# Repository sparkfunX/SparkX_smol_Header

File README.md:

# SparkX smôl Header

[*SparkX smôl Header (SPX-18361)*](https://www.sparkfun.com/products/18361)

A header to break out the smôl FPC connections.

## Repository Contents

- **/Hardware** - Eagle design files
- **LICENSE.md** contains the licence information

## Product Versions

- [SPX-18361](https://www.sparkfun.com/products/18361) - Original SparkX Release.

## License Information

This product is _**open source**_!

Please review the LICENSE.md file for license information.

If you have any questions or concerns on licensing, please contact technical support on our [SparkFun forums](https://forum.sparkfun.com/viewforum.php?f=123).

Distributed as-is; no warranty is given.

- Your friends at SparkFun.

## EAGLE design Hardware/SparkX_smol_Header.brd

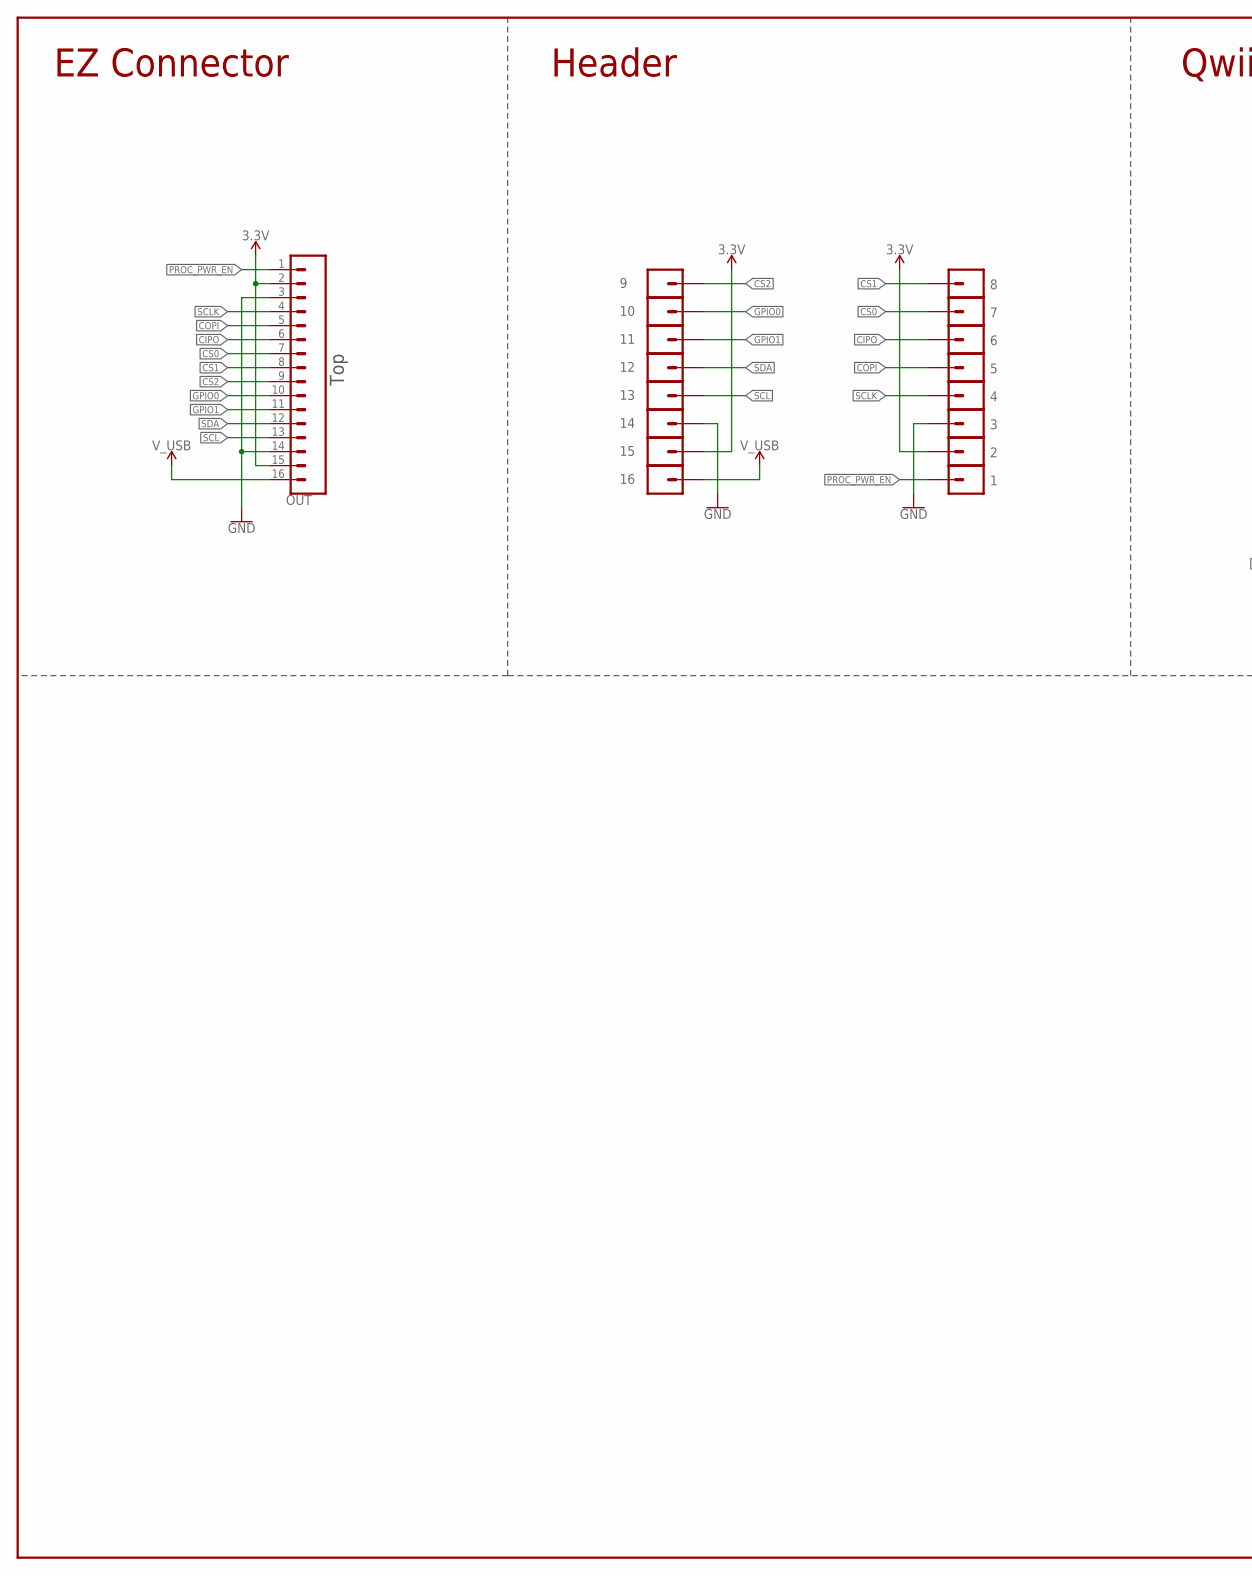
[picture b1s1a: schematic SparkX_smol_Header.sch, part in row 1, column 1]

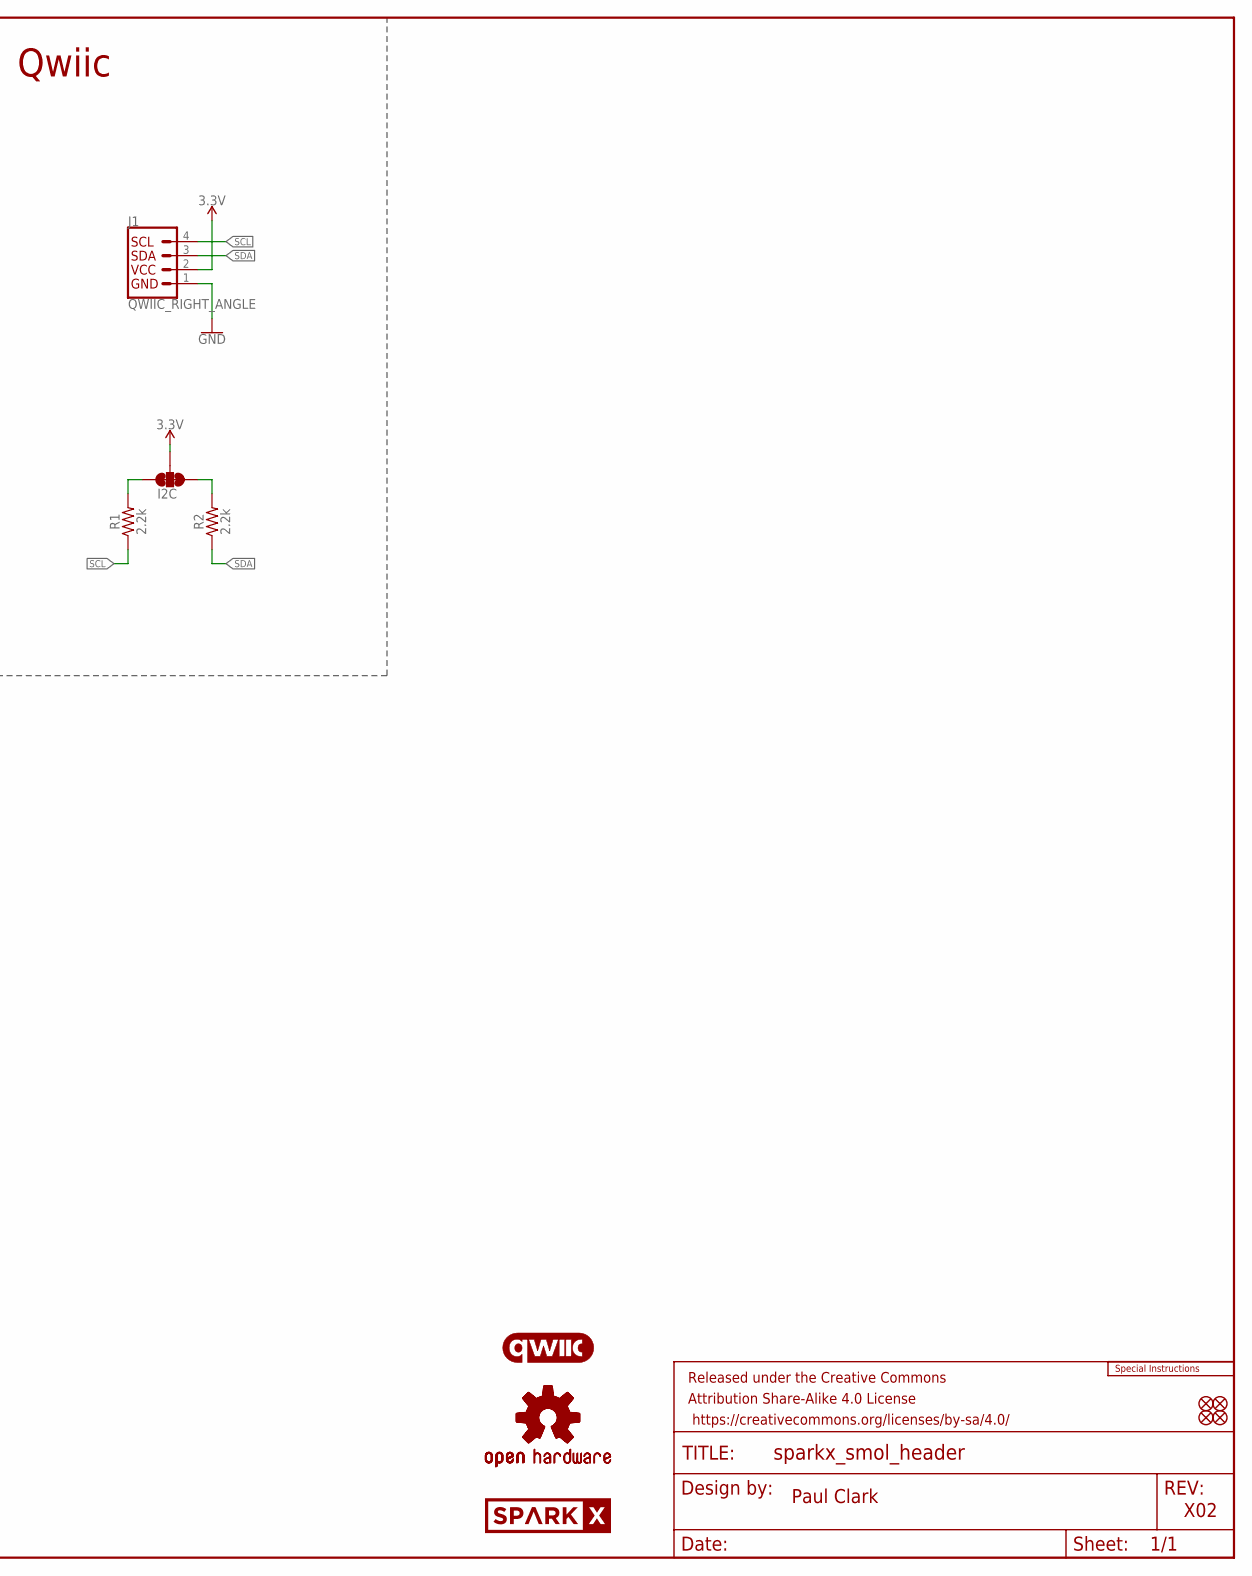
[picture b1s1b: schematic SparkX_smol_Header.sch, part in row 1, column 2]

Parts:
1, 2, 3, 4, 5, 6, 7, 8, 9, 10, 11, 12, 13, 14, 15, 16: CONN_01PTH_NO_SILK_YES_STOP; 1X01_NO_SILK
FD1, FD2, FD3, FD4: FIDUCIALUFIDUCIAL; FIDUCIAL-MICRO
FRAME1: FRAME-LEDGER; CREATIVE_COMMONS
I2C: JUMPER-SMT_3_2-NC_TRACE_SILK; SMT-JUMPER_3_2-NC_TRACE_SILK
J1: QWIIC_RIGHT_ANGLE; JST04_1MM_RA
LOGO1: SPECIAL_INSTRUCTIONS-ORDERING; ORDERING_INSTRUCTIONS
LOGO2, LOGO3: OSHW-LOGOMINI; OSHW-LOGO-MINI
LOGO4: QWIIC_LOGO_5MM; QWIIC_5MM
OUT: CONN_16FPC_16_0.5MM; FPC_16_0.5MM
R1, R2: 2.2k; 0603
U$1: SPARKX-LOGO3; SPARKX-SMALL

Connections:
3.3V: 2.1, 15.1, I2C.2, J1.2, OUT.2, OUT.15
CIPO: 6.1, OUT.6
COPI: 5.1, OUT.5
CS0: 7.1, OUT.7
CS1: 8.1, OUT.8
CS2: 9.1, OUT.9
GND: 3.1, 14.1, J1.1, OUT.3, OUT.14
GPIO0: 10.1, OUT.10
GPIO1: 11.1, OUT.11
unnamed: I2C.3, R1.2
unnamed: I2C.1, R2.2
PROC_PWR_EN: 1.1, OUT.1
SCL: 13.1, J1.4, OUT.13, R1.1
SCLK: 4.1, OUT.4
SDA: 12.1, J1.3, OUT.12, R2.1
V_USB: 16.1, OUT.16

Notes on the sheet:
Paul Clark
X02
EZ Connector
Top
Header
Qwiic

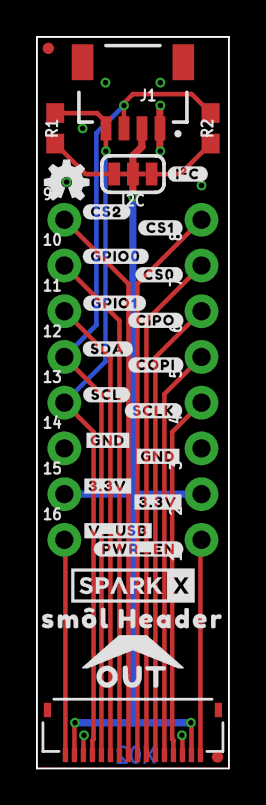
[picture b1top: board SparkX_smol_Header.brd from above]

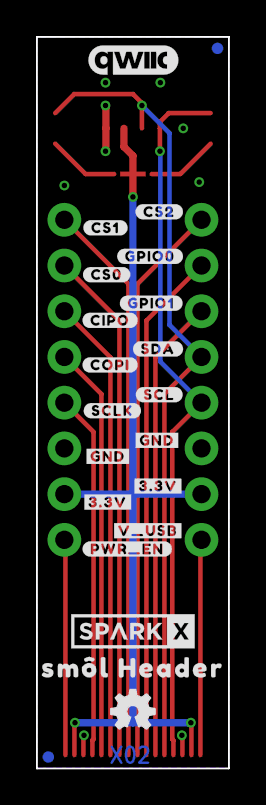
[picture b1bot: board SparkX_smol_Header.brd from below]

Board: 2 copper layers, 10.7 x 40.6 mm, 68 parts (22 on the bottom side), 16 nets.

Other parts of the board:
U$2, U$4, U$23, U$24: #3#3V#0
U$3, U$22: #V_USB#0
U$5, U$25: #PWR_EN#0
U$6, U$7, U$26, U$27: #GND#0
U$8, U$28: #SCLK#0
U$9, U$38: #SCL#0
U$10, U$29: #COPI#0
U$11, U$30: #SDA#0
U$12, U$31: #CIPO#0
U$13, U$21: SM�L_HEADER0
U$14, U$32: #GPIO1#0
U$15, U$33: #CS0#0
U$16, U$34: #GPIO0#0
U$17, U$35: #CS1#0
U$18, U$36: #CS2#0
U$19: #I�C#0
U$20: SPARKX-LOGO3; SPARKX-SMALL
U$37: OUT0

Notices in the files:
parts and their libraries:
SparkFun-Aesthetics: Licensing: Creative Commons ShareAlike 4.0 International - https://creativecommons.org/licenses/by-sa/4.0
SparkFun-Aesthetics: Released under the Creative Commons Attribution Share-Alike 4.0 License
SparkFun-Aesthetics: https://creativecommons.org/licenses/by-sa/4.0
